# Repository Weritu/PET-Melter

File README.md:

# PET-Melter
Repositório criado parar armazenar arquivos importantes e referentes a montagem e desenvolvimento do TCC Manufatura Aditiva: O Upcycling de Garrafas PET.

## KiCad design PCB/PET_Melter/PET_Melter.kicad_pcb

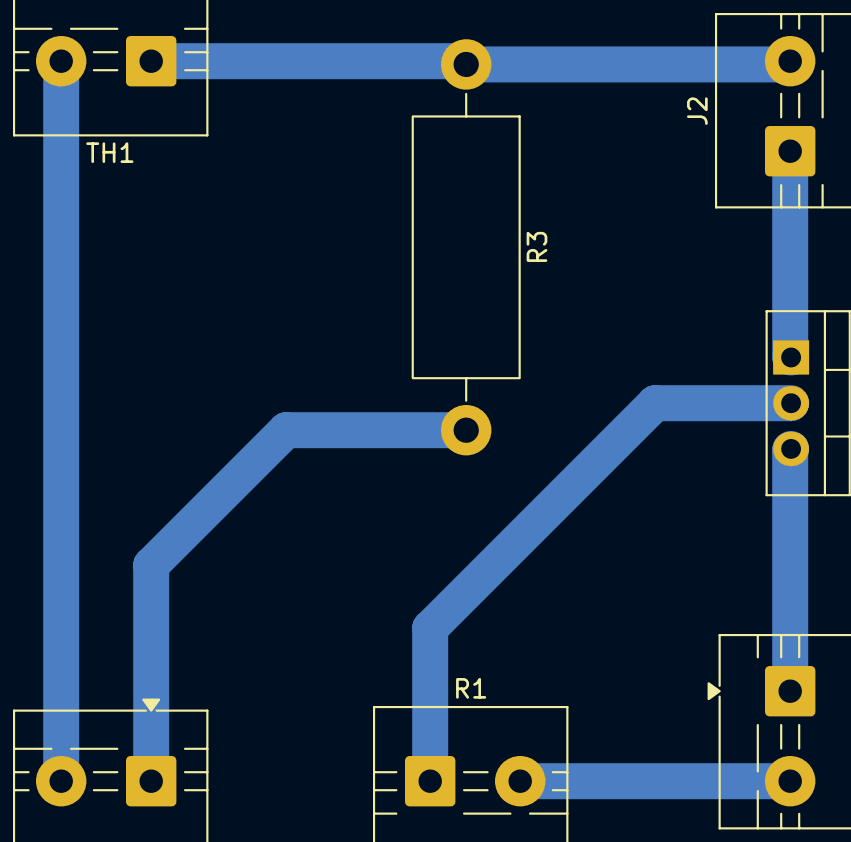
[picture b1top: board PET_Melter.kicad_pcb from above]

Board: 2 copper layers, 7 parts (0 on the bottom side), 7 nets.

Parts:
J1: BorneAlimentação; TerminalBlock_MaiXu_MX126-5.0-02P_1x02_P5.00mm
J2: BorneArduino; TerminalBlock_MaiXu_MX126-5.0-02P_1x02_P5.00mm
J3: BorneAlimArduino; TerminalBlock_MaiXu_MX126-5.0-02P_1x02_P5.00mm
Q1: IRLZ44N; TO-220-3_Vertical
R1: Heater; TerminalBlock_MaiXu_MX126-5.0-02P_1x02_P5.00mm
R3: 100KΩ; R_Axial_DIN0614_L14.3mm_D5.7mm_P20.32mm_Horizontal
TH1: Thermistor; TerminalBlock_MaiXu_MX126-5.0-02P_1x02_P5.00mm

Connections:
+5V: J3.1, R3.2
A0: J2.2, R3.1, TH1.1
D6: J2.1, Q1.1 (G)
GND: J3.2, TH1.2
unnamed: J1.1, Q1.3 (S)
unnamed: J1.2, R1.2
unnamed: Q1.2 (D), R1.1

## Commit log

2025-12-09 Código principal PETMelter
    Código fonte com a lógica para o funcionamento da máquina.
2025-12-09 TCC Completo.
    Documento referente ao TCC.
2025-12-09 PCB PETMelter.
    PCB com componentes referente a eletrônica do projeto.
